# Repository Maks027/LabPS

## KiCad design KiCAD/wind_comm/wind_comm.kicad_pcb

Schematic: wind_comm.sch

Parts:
C1, C9: 2200uF, 63V; CP_Radial_D18.0mm_P7.50mm
C2, C4: 1uF, 63V; C_Rect_L10.3mm_W7.2mm_P7.50mm_MKS4
C3: 1uF, 63V; C_Rect_L10.3mm_W5.0mm_P7.50mm_MKS4
C5, C6, C10: 330uF, 16V; CP_Radial_D6.3mm_P2.50mm
D1: GBJ2510; Diode_Bridge_Vishay_GBJ
D4, D5, D6, D7, D9, D15, D16, D17: SMA4007; D_SMA_Handsoldering
D8, D11: 15V; D_DO-41_SOD81_P7.62mm_Horizontal
J1, J10: Winding 3; TerminalBlock_bornier-2_P5.08mm
J2: Winding 2; TerminalBlock_bornier-2_P5.08mm
J3: OUT_V; TerminalBlock_bornier-2_P5.08mm
J4: Winding 1; TerminalBlock_bornier-2_P5.08mm
J5: Switch Connector; TerminalBlock_bornier-3_P5.08mm
J6: Volatge Feedback; TerminalBlock_bornier-2_P5.08mm
J9: OUT_GND; TerminalBlock_bornier-2_P5.08mm
J11: 12V_OUT; TerminalBlock_bornier-2_P5.08mm
K1, K2, K3, K4: SRA-12VDC-CL
MH1, MH2, MH3, MH4: MountingHole; MountingHole_3.2mm_M3_ISO7380
Q2, Q3, Q4, Q5: MMBT5551L; SOT-23
R1, R2, R7: 10K; R_1206_3216Metric_Pad1.42x1.75mm_HandSolder
R3, R4: 2K; R_1206_3216Metric_Pad1.42x1.75mm_HandSolder
R5, R6: 1K; R_1206_3216Metric_Pad1.42x1.75mm_HandSolder
TP1: LED2_A; TestPoint_THTPad_2.0x2.0mm_Drill1.0mm
TP2: LED1_A; TestPoint_THTPad_2.0x2.0mm_Drill1.0mm
TP3, TP4: LED2_K; TestPoint_THTPad_D2.0mm_Drill1.0mm
U1: L7812; TO-220-3_Vertical

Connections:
+12V: C4.1, J5.2, J11.1, U1.3 (OUT)
/GR1: D4.1, D5.1, J5.1, K3.4, K4.4, R1.1, R2.1, TP1.1
/GR2: D6.1, D7.1, J5.3, K1.4, K2.4, TP2.1
/OUT: C1.1, C2.1, C9.1, D1.1 (+), J3.1, J3.2
/W11: D1.3 (~~), J4.2, K4.3
/W12: J4.1, K2.3
/W21: J2.2, K2.2, K3.3, K4.2
/W22: J2.1, K1.3, K2.1
/W31: J1.2, K1.2, K3.2
/W32: D1.2 (~~), J1.1, K1.1
GND: C1.2, C2.2, C3.2, C4.2, C5.2, C6.2, C9.2, C10.2, D1.4 (-), D16.2, D17.2, J6.2, J9.1, J9.2, J11.2, Q2.2 (E), Q3.2 (E), Q4.2 (E), Q5.2 (E), R3.2, R4.2, R7.2, U1.2 (GND)
unnamed: C5.1, Q2.1 (B), R1.2
unnamed: C6.1, Q3.1 (B), R2.2
unnamed: C3.1, C10.1, D9.1, D15.1, U1.1 (IN)
unnamed: D4.2, K4.5, Q3.3 (C)
unnamed: D5.2, K3.5, Q2.3 (C)
unnamed: D6.2, K2.5, Q4.3 (C)
unnamed: D7.2, K1.5, Q5.3 (C)
unnamed: D8.1, J6.1
unnamed: D8.2, D11.1, R5.2
unnamed: D11.2, R6.2, R7.1
unnamed: D15.2, D17.1, J10.2
unnamed: D9.2, D16.1, J10.1
unnamed: Q4.1 (B), R5.1
unnamed: Q5.1 (B), R6.1
unnamed: R3.1, TP3.1
unnamed: R4.1, TP4.1

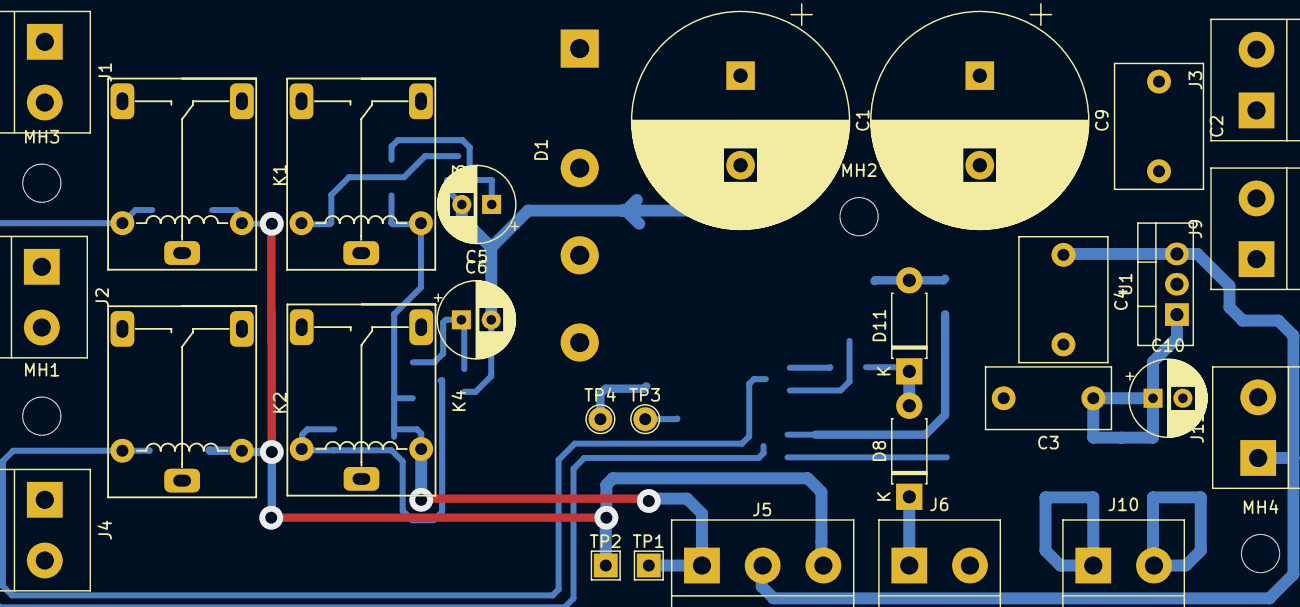
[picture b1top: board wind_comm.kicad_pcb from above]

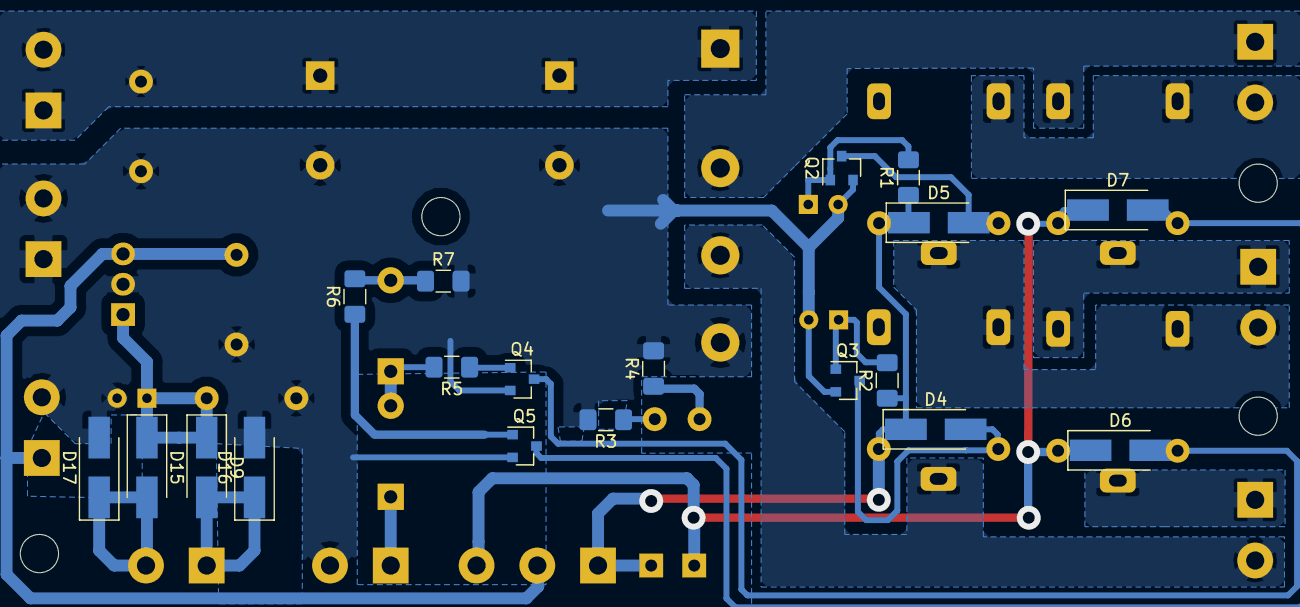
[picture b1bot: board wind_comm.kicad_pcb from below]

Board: 2 copper layers, 52 parts (19 on the bottom side), 27 nets.

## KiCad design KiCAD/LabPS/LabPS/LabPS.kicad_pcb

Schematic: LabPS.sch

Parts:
C1: 10uF, 63V; CP_Radial_D5.0mm_P2.50mm
C2: 0.56uF; C_Rect_L13.0mm_W5.0mm_P10.00mm_FKS3_FKP3_MKS4
C4, C9, C10: 100nF; C_1206_3216Metric_Pad1.42x1.75mm_HandSolder
C5: 10nF; C_1206_3216Metric_Pad1.42x1.75mm_HandSolder
C6: 1nF; C_1206_3216Metric_Pad1.42x1.75mm_HandSolder
C7, C8: 1uF; C_1206_3216Metric_Pad1.42x1.75mm_HandSolder
D1, D3: ES3G; D_SMC_Handsoldering
D5: TL431DBZ; SOT-23
J1, J2: 1K; TerminalBlock_bornier-2_P5.08mm
J4: 5K; TerminalBlock_bornier-3_P5.08mm
J5: 10K; TerminalBlock_bornier-3_P5.08mm
Q1: 2SC5200; TO-3P-3_Vertical
Q2: BD140; TO-126-3_Vertical
Q3, Q4, Q5: MMBT5551; SOT-23
R1, R4, R18, R22: 1K; R_1206_3216Metric_Pad1.42x1.75mm_HandSolder
R2, R8: 39K; R_1206_3216Metric_Pad1.42x1.75mm_HandSolder
R3: 4.3K, 1W; R_Axial_DIN0414_L11.9mm_D4.5mm_P5.08mm_Vertical
R5: 9.1K; R_1206_3216Metric_Pad1.42x1.75mm_HandSolder
R6: 1.2K; R_1206_3216Metric_Pad1.42x1.75mm_HandSolder
R7: 100K; R_1206_3216Metric_Pad1.42x1.75mm_HandSolder
R9: 5.6K, 1W; R_Axial_DIN0414_L11.9mm_D4.5mm_P7.62mm_Vertical
R10: 2.7K; R_1206_3216Metric_Pad1.42x1.75mm_HandSolder
R11: 4.7K; R_1206_3216Metric_Pad1.42x1.75mm_HandSolder
R12, R13, R14, R15, R17: 10K; R_1206_3216Metric_Pad1.42x1.75mm_HandSolder
R16: 510K; R_1206_3216Metric_Pad1.42x1.75mm_HandSolder
R19: 1R; R_1206_3216Metric_Pad1.42x1.75mm_HandSolder
R20: 20K; R_1206_3216Metric_Pad1.42x1.75mm_HandSolder
R21: 0,05R, 2W; R_Axial_DIN0516_L15.5mm_D5.0mm_P20.32mm_Horizontal
RV1, RV2: 2K; Potentiometer_Piher_PT-6-V_Vertical
TP1, TP2, TP3: TestPoint; TestPoint_THTPad_2.0x2.0mm_Drill1.0mm
TP4: G_LED_A; TestPoint_THTPad_2.0x2.0mm_Drill1.0mm
TP5: G_LED_K; TestPoint_THTPad_2.0x2.0mm_Drill1.0mm
TP6: R_LED_A; TestPoint_THTPad_2.0x2.0mm_Drill1.0mm
TP7: R_LED_K; TestPoint_THTPad_2.0x2.0mm_Drill1.0mm
U1: LM324

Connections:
+12V: C7.2, Q3.2 (E), R6.2, R8.1, R10.1, R16.1, U1.4 (V+)
/S_GND: C1.2, C2.2, C7.1, C8.1, C10.2, D3.2, D5.3, J2.1, J5.3, Q4.2 (E), R12.2, R17.2, R18.2, R20.2, R21.1, RV1.2, RV1.3
/U_IN: D1.1, J1.1, Q1.2, Q2.1, Q3.3 (C), R3.1, R4.1
/U_OUT: C1.1, C2.1, D1.2, D3.1, J2.2, Q1.3, R1.1, R2.1
GND: J1.2, Q5.3 (C), R19.1, R21.2, TP5.1, U1.11 (V-)
I_LIM: C4.1, J5.1, R13.2, U1.14
unnamed: C4.2, R7.2
unnamed: C5.1, R15.1, U1.8
unnamed: C5.2, R11.2
unnamed: C6.1, D5.2, R8.2, R17.1
unnamed: C6.2, D5.1, Q3.1 (B), R3.2
unnamed: C8.2, J4.2, U1.12 (+)
unnamed: C9.1, R14.1, U1.3 (+)
unnamed: C9.2, R22.1, TP7.1, U1.1
unnamed: C10.1, J5.2, U1.10 (+)
unnamed: J4.1, R16.2
unnamed: J4.3, R19.2
unnamed: Q1.1, Q2.2, R1.2
unnamed: Q2.3, R4.2, R9.1
unnamed: Q4.1 (B), R15.2, R18.1
unnamed: Q4.3 (C), R9.2
unnamed: Q5.1 (B), R22.2
unnamed: Q5.2 (E), R6.1, TP4.1, TP6.1
unnamed: R5.1, RV1.1
unnamed: R10.2, RV2.1
unnamed: R2.2, R5.2, R11.1, U1.9 (-)
unnamed: R7.1, R12.1, U1.13 (-)
unnamed: R13.1, U1.2 (-)
unnamed: R14.2, RV2.2
unnamed: R20.1, RV2.3
unnamed: TP1.1, U1.6 (-)
unnamed: TP2.1, U1.7
unnamed: TP3.1, U1.5 (+)

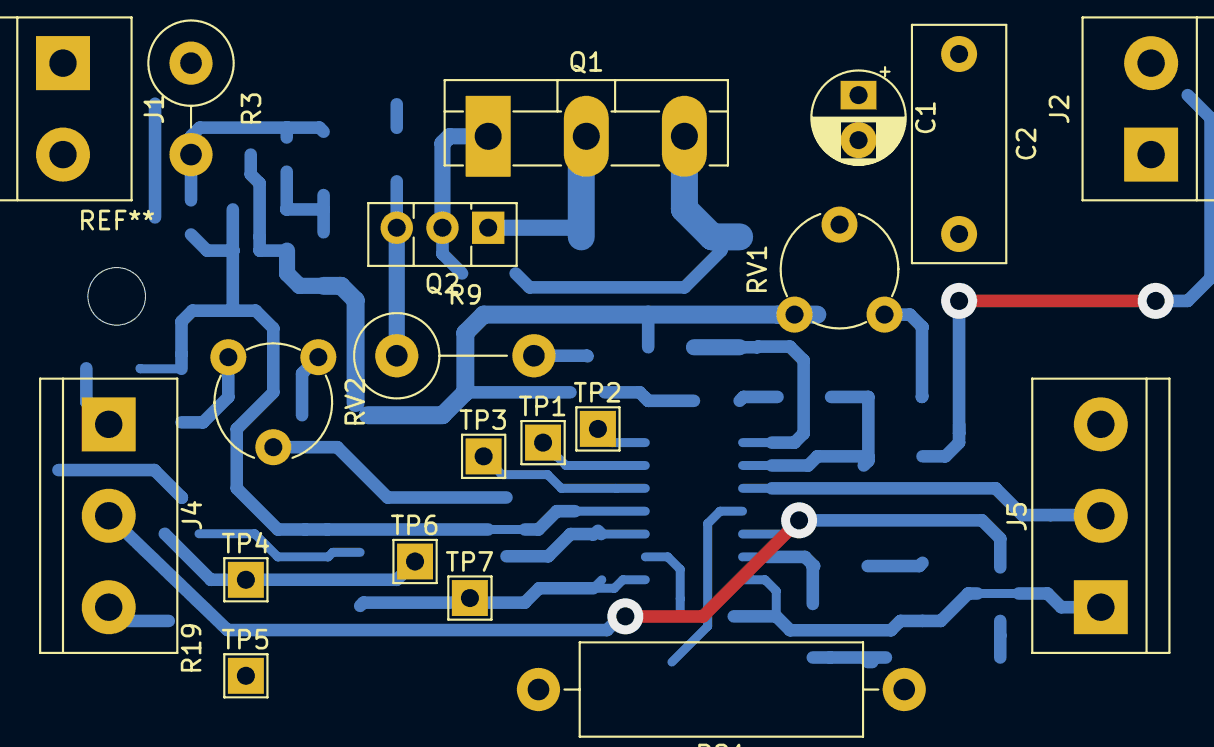
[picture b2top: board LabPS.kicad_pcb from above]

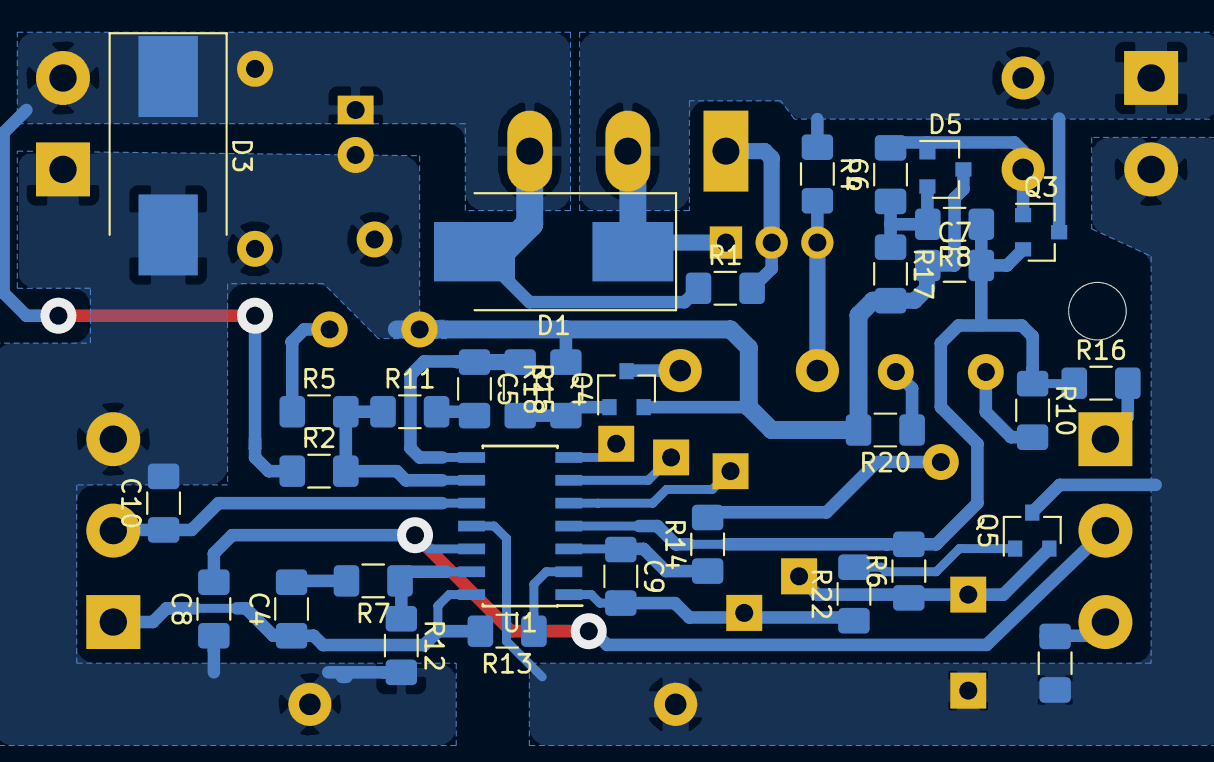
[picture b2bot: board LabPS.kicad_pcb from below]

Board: 2 copper layers, 53 parts (33 on the bottom side), 33 nets.

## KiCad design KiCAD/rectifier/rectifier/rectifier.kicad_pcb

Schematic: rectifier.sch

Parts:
C1: 330uF, 16V; CP_Radial_D6.3mm_P2.50mm
D1, D2, D3, D4: SM4007; D_MELF
J1, J2: Screw_Terminal_01x02; TerminalBlock_bornier-2_P5.08mm

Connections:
unnamed: C1.1, D1.1 (K), D2.1 (K), J2.1
unnamed: C1.2, D3.2 (A), D4.2 (A), J2.2
unnamed: D1.2 (A), D3.1 (K), J1.1
unnamed: D2.2 (A), D4.1 (K), J1.2

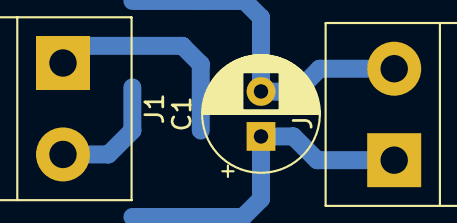
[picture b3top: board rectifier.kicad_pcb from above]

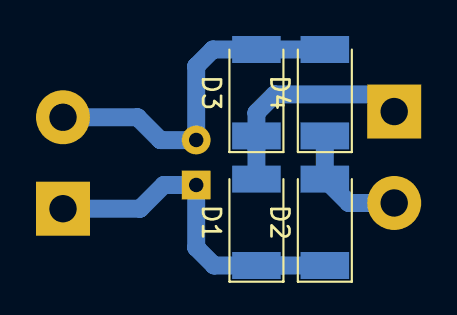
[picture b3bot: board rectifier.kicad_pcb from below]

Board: 2 copper layers, 7 parts (4 on the bottom side), 4 nets.

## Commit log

2020-04-28 Init
2020-04-28 Fixed uControl
